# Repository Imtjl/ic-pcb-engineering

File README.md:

# IC & PCB Engineering

> Schematic design, PCB layout, hybrid integrated circuits — coursework demonstrating end-to-end hardware design workflow.

## Overview

This repository showcases practical work in **integrated circuit and printed circuit board engineering**, covering the full hardware design pipeline: from circuit analysis and component selection to multi-layer PCB routing, design rule verification, and 3D presentation.

The work is organized into two parts:

- **Part 1 — Hybrid Integrated Circuits**: film-based resistors, capacitors, and transistor integration
- **Part 2 — Multi-Layer PCB Design**: complete schematic-to-board workflow with custom-authored design documentation

### Self-Authored Design Guide

> [!IMPORTANT]
> A comprehensive PCB design guide ([`hw2/guide.pdf`](hw2/guide.pdf)) authored from scratch, covering the complete schematic-to-PCB workflow. Created independently in absence of official course materials.

This guide is reusable for any KiCad-based PCB design workflow and represents original technical documentation work beyond the course requirements.

---

## Showcase

### Schematic Design

#### Custom advanced schematics

##### Multi chip lab board

||
|-|

- source: [lab_pcb_v2.pdf](https://github.com/user-attachments/files/28438125/Earlink_lab_v1.2.pdf)

##### qa dut lab board

||
|-|

#### course schematics

|||
|-|-|

### PCB Layouts

|||
|-|-|
|||
|||
|||

### 3D Renders

**Improved design (with & without solder mask)**

#### Racer howl superlight PRO MAX

|||
|-|-|
|||

#### "Living in NY"

|||
|-|-|
|||

#### Compact v2

|||
|-|-|
|||

#### Circular madness

||||
|-|-|-|

#### First manual design

|||
|-|-|
|||

### Hybrid Integrated Circuits

**Film resistors, capacitors, and transistors**

|||
|-|-|
|||

## Engineering Skills

| Skill | Detail |
|---|---|
| **Schematic Design** | Circuit analysis, component selection, topology optimization |
| **PCB Layout** | Two-layer board routing with freerouting plugin, DRC verification, EMI mitigation via copper pour |
| **Hybrid IC Design** | Film-based component integration (resistors, capacitors, transistors) |
| **3D Visualization** | Photorealistic rendering for design validation and presentation |
| **Technical Documentation** | Self-authored, reusable PCB design guideline (see `hw2/guide.pdf`) |

## Tools

KiCad · Freerouting · 3D Rendering Pipeline

---

<sub>Developed as part of the Computer-Aided Design Systems course at ITMO University, Faculty of Software Engineering and Computer Systems. Repository scope and documentation authored independently.</sub>

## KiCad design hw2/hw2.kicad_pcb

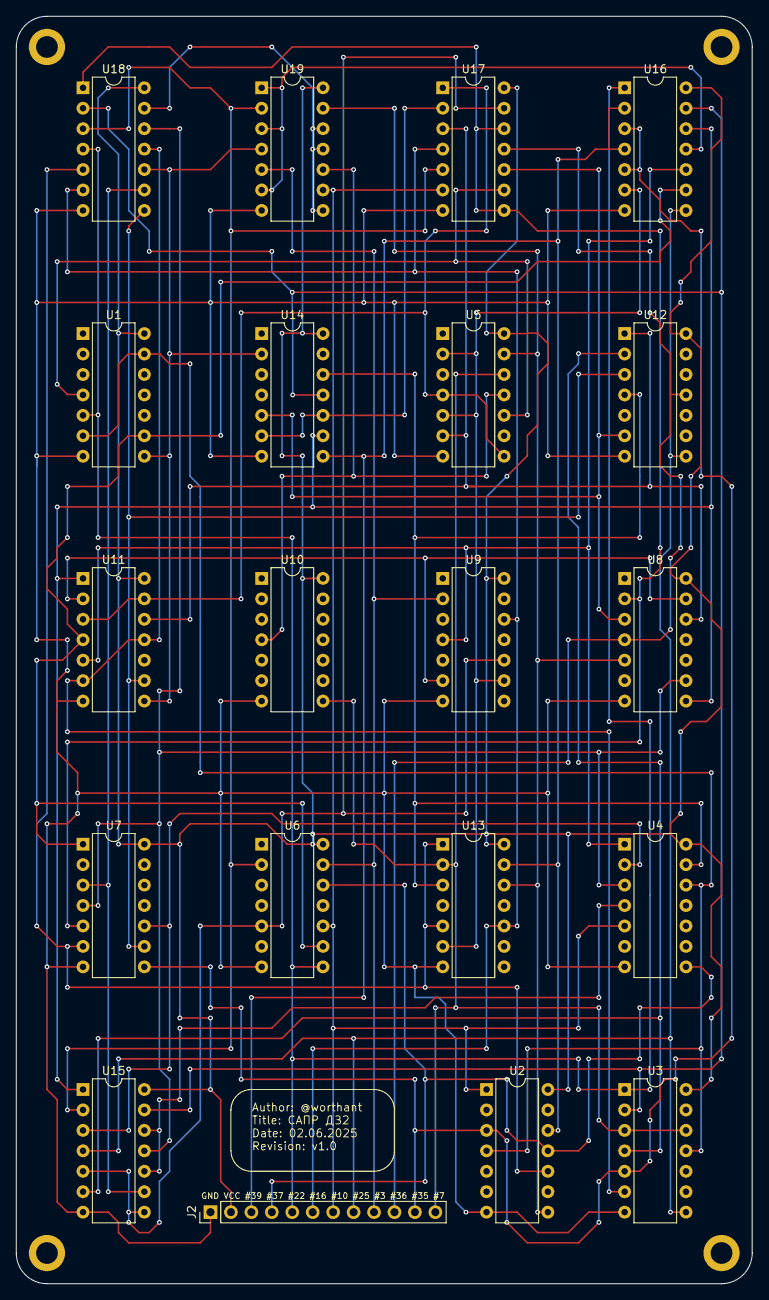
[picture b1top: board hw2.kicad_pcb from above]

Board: 2 copper layers, 91.4 x 157.5 mm, 20 parts (0 on the bottom side), 41 nets.

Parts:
J2: PinHeader_1x12_P2.54mm_Vertical
U1, U2, U3, U4, U5, U6, U7, U8, U9, U10, U11, U12, U13, U14, U15, U16, U17, U18, U19: DIP-14_W7.62mm

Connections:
#1: U1.8, U11.8, U14.2, U18.10, U19.4
#2: U7.3, U15.9, U18.9
#3: J2.9, U6.13, U9.2, U19.5
#4: U5.2, U5.5, U9.9, U13.6, U16.6
#5: U16.11, U19.1, U19.3, U19.6
#6: U2.8, U5.13, U8.5, U13.12, U19.13
#7: J2.12, U3.3, U3.12, U5.12, U10.8, U13.2
#8: U2.10, U7.6, U13.1, U13.5, U18.5
#9: U6.2, U15.2, U17.5, U18.3, U19.2
#10: J2.7, U2.1, U4.5, U6.10, U17.6, U19.9
#11: U5.11, U10.4, U19.10
#12: U18.13, U19.8, U19.11, U19.12
#13: U8.3, U12.6, U14.5, U17.10
#14: U8.13, U9.6, U11.2
#15: U7.9, U11.9, U12.3, U18.8
#16: J2.6, U9.12, U13.10, U17.4, U18.6
#17: U3.2, U14.11, U15.13, U16.13, U18.2
#18: U4.2, U7.10, U15.3
#19: U4.13, U12.4, U13.3, U14.12
#20: U7.5, U8.2, U17.8, U17.12, U18.1
#21: U3.6, U11.6, U11.11, U18.11
#22: J2.5, U1.5, U3.1, U6.8, U16.1, U18.4
#23: U4.3, U7.4, U8.9, U15.11, U18.12
#24: U14.6, U14.10, U17.2
#25: J2.8, U3.8, U12.8, U15.4, U16.8
#26: U4.1, U9.4, U11.5, U16.10
#27: U5.6, U8.12, U11.12, U12.1, U17.3
#28: U1.4, U5.10, U17.9
#29: U8.8, U11.1, U14.9, U15.1, U16.12
#30: U3.4, U12.2, U15.6
#31: U4.4, U15.10, U15.12
#32: U6.5, U9.10, U15.5, U15.8, U17.13
#33: U5.4, U5.8, U11.3, U11.13, U17.1
#34: U1.6, U1.13, U2.4, U3.11, U4.12
#35: J2.11, U2.3, U3.5, U7.8, U16.3, U16.5
#36: J2.10, U8.4, U12.11, U17.11
#37: J2.4, U2.11, U4.8, U6.12
#38: U1.9, U6.9, U7.1, U11.4, U16.9
#39: J2.3, U2.12, U13.13, U14.8, U16.2, U16.4
GND: J2.1, U1.7, U2.7, U3.7, U4.7, U5.7, U6.7, U7.7, U8.7, U9.7, U10.7, U11.7, U12.7, U13.7, U14.7, U15.7, U16.7, U17.7, U18.7, U19.7
VCC: J2.2, U1.14, U2.14, U3.14, U4.14, U5.14, U6.14, U7.14, U8.14, U9.14, U10.14, U11.14, U12.14, U13.14, U14.14, U15.14, U16.14, U17.14, U18.14, U19.14

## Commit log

2025-05-02 :ledger: docs!: All course literature
2025-05-02 :hammer: feat(hw1): All calculations
2025-05-03 :hammer: feat(hw1): Calculate rounding error
2025-05-23 :hammer: feat(hw1): Homework1 done :tada:
2025-05-23 :wrench: chore(.gitignore): Ignore LaTeX files & pdf's
2025-05-23 :hammer: wip(hw2): hw2 description
2025-06-03 :hammer: feat(hw2): PCB done :tada:
2025-06-03 :hammer: feat(hw2): Upload methodological reference, allow in gitignore
2025-06-12 :hammer: feat(hw1): Automate calculations
2025-06-12 :recycle: refactor(hw2): Compress KiCad projects to .zip
2025-06-12 :hammer: feat(hw2): Add new completed hw2 variant
2025-06-12 :hammer: feat(hw2): Add completed var38
2025-06-13 :hammer: feat(hw1): Enhance calculation flow
2025-06-13 :ledger: docs(readme): Create course overview & showcase
2025-06-19 :hammer: feat(hw1): Add completed var47
2025-06-19 :ledger: docs(readme): Showcase new hw2 pcb design
2025-06-19 :hammer: WIP(auto-hw2): Automate hw2 net creation
2025-06-20 :hammer: feat(auto-hw2): Manual OCR + automated var47,49,50 netlist
2025-06-20 :hammer: feat(hw2): Add completed var49, var50
2025-06-20 :ledger: docs(readme): Showcase new designs
2025-06-20 :wrench: chore(hw2): Add copper pour variation for var49
2025-06-20 :ledger: docs(readme): Showcase circular madness design
2025-06-28 :hammer: feat(hw1): Add schema9-var2 calculations & account for precision
2025-06-28 :hammer: feat(hw1): Add schema13-var2 calc + neat tabulate lib
2025-06-28 :ledger: docs(readme): New hybrid integrated circuits :tada:
2025-09-04 :hammer: feat(hw1): Add schema23-var2 calculation with latest advances techniques
2025-09-04 :hammer: feat(hw2): Add var46 automated net creation script
2025-09-12 :ledger: docs(readme): New PCB design :tada:
2025-09-12 :hammer: feat(hw2): Add var53 automated design + kicad project
2025-09-12 :hammer: feat(hw1): Add schema15-var2 calc with latest advanced techniques
2026-04-12 :hammer: feat(hw1): Automate calculation
2026-04-12 :hammer: feat(hw1-auto): vibecode semi-automation
2026-04-16 :hammer: feat(hw1): Add schema19-var2 calc
2026-04-16 :wrench: chore(hw1-auto): schema19-var2 test
2026-04-23 :hammer: feat(hw2): Add var50-2 automated design
2026-04-23 :hammer: feat(hw2): Add var50-2-v2 project archive
2026-05-31 :ledger: docs(readme): Update schematics progress
